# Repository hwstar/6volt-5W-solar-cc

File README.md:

***6volt-5W-solar-cc***
=============

This is a solar charge controller for use with 5 watt 6 volt solar panels.

**Introduction**

The project use a custom printed circuit board for the charge controller
power management electronics, and requires an external Arduino pro mini
to run the control firmware.

Setup in the lab:

The power management board design has the following features:

* PV input transient and reverse polarity protection
* Sensing for PV input voltage, converter output current, load current,
and battery voltage.
* PV Back feed protection using a dedicated MOSFET.
* PTC and reverse polarity protection on the battery connector.
* 3 sets of 3 pin connectors for loads. 
* 4 pin sense connector for current and voltage sensing to the Arduino
* 6 pin control connector for control signals from the Arduino
* Dedicated MOSFET for load switching.
* Switched and unswitched load configuration using solder jumpers.
* Double sided circuit board 5cm X 5cm

Front view of board:

Rear view of board:

**Board Blanks**

Board blanks are available on Tindie:

https://www.tindie.com/products/hwstarsr/6-volt-5-watt-solar-charge-controller

**Firmware**

The firmware is hosted as a separate project on my github pages.
See [fw-6volt-5W-solar-cc](https://github.com/hwstar/fw-6volt-5W-solar-cc). For more details on
the firmware features, please visit the firmware page.

**Python/tkinter utility**

A Python/tkinter utility is available to download variables from the
charge controller in real time using a Bus Pirate and an I2C interface.
This is also hosted on my github pages under 
[chargectrlr-python-buspirate](https://github.com/hwstar/chargectrlr-python-buspirate).

**License**

CC-BY-SA

**Disclaimer**

This project uses a lead acid battery. Please observe all safety 
precautions listed on the battery. Enclose this project in a metallic
fireproof enclosure. Keep internal temperatures within the operating
limits of the battery. Not responsible for life, or loss of property
under any circumstance!

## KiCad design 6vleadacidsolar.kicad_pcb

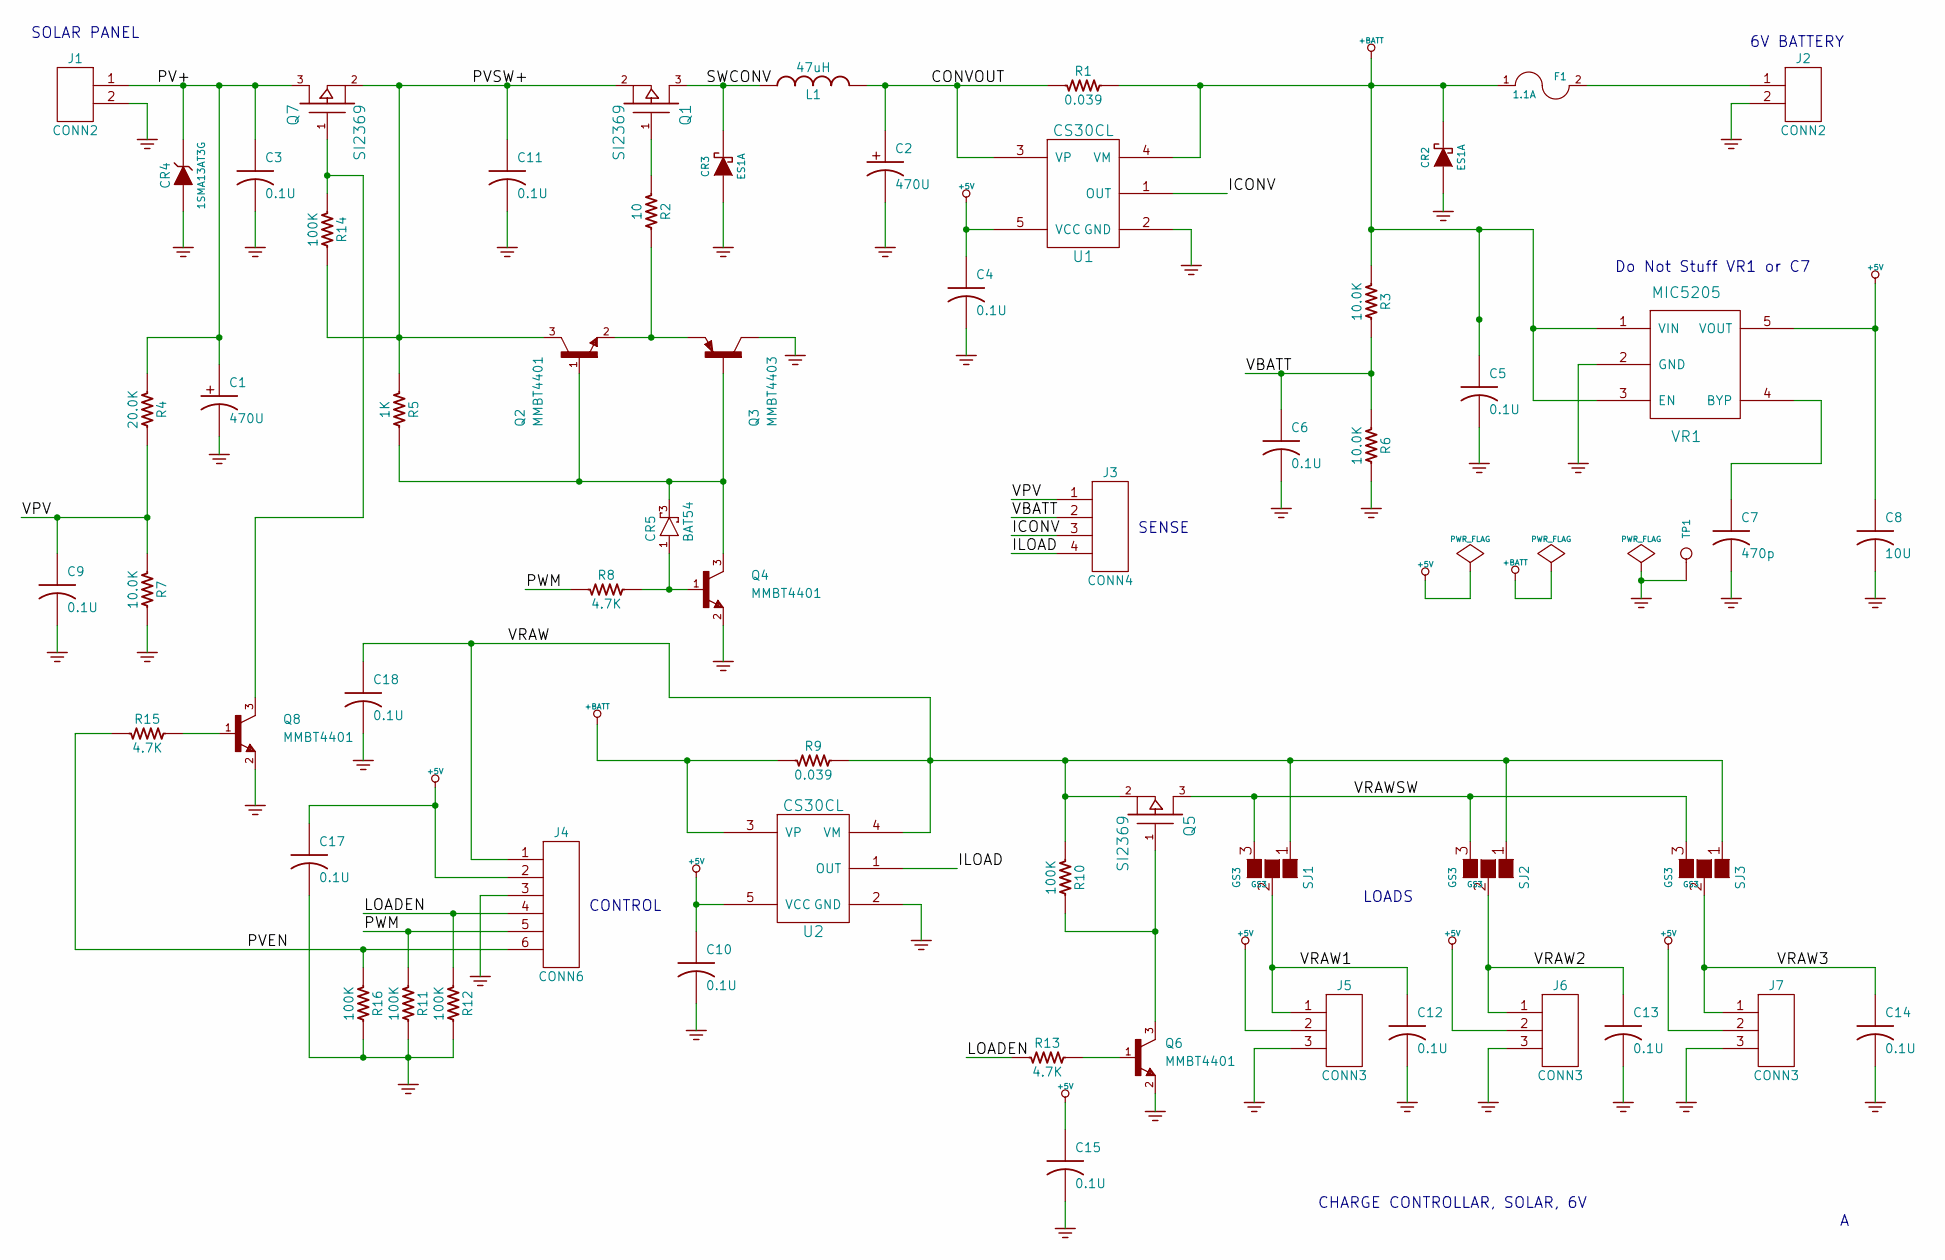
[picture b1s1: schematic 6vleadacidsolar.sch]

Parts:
C1, C2: 470U; MPN EMZJ160ADR471MHA0G
C3, C4, C5, C6, C9, C10, C11, C12, C13, C14, C15, C17, C18: 0.1U
C7: 470p
C8: 10U
CR2, CR3: ES1A; MPN ES1A-E3/61T
CR4: 1SMA13AT3G; MPN 1SMA13AT3G
CR5: BAT54; SOT23
F1: 1.1A; MPN MINISMD160F
J1, J2: CONN2
J3: CONN4
J4: CONN6
J5, J6, J7: CONN3
L1: 47uH; MPN SDE0805A-470K
Q1, Q5, Q7: SI2369; MPN SI2369DS-T1-E3
Q2, Q4, Q6, Q8: MMBT4401; SOT23
Q3: MMBT4403; custom-SOT23
R1, R9: 0.039; MPN KRL1220E-M-R039-F-T5
R2: 10
R3, R6, R7: 10.0K
R4: 20.0K
R5: 1K
R8, R13, R15: 4.7K
R10, R11, R12, R14, R16: 100K
SJ1, SJ2, SJ3: GS3
TP1: CONN_1
U1, U2: CS30CL; MPN CS30CL
VR1: MIC5205; SOT23-5

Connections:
+5V: C4.1, C8.1, C10.1, C15.1, C17.1, J4.2, J5.2, J6.2, J7.2, U1.5 (VCC), U2.5 (VCC), VR1.5 (VOUT)
+BATT: C5.1, CR2.2 (K), F1.1, R1.2, R3.1, R9.1, U1.4 (VM), U2.3 (VP), VR1.1 (VIN), VR1.3 (EN)
/CONVOUT: C2.1, L1.2, R1.1, U1.3 (VP)
/ICONV: J3.3, U1.1 (OUT)
/ILOAD: J3.4, U2.1 (OUT)
/LOADEN: J4.4, R12.1, R13.1
/PV+: C1.1, C3.1, CR4.2 (K), J1.1, Q7.3 (D), R4.1
/PVEN: J4.6, R15.1, R16.1
/PVSW+: C11.1, Q1.2 (S), Q2.3 (C), Q7.2 (S), R5.1, R14.2
/PWM: J4.5, R8.1, R11.1
/SWCONV: CR3.2 (K), L1.1, Q1.3 (D)
/VBATT: C6.1, J3.2, R3.2, R6.1
/VPV: C9.1, J3.1, R4.2, R7.1
/VRAW: C18.1, J4.1, Q5.2 (S), R9.2, R10.1, SJ1.1 (G1), SJ2.1 (G1), SJ3.1 (G1), U2.4 (VM)
/VRAW1: C12.1, J5.1, SJ1.2 (G2)
/VRAW2: C13.1, J6.1, SJ2.2 (G2)
/VRAW3: C14.1, J7.1, SJ3.2 (G2)
/VRAWSW: Q5.3 (D), SJ1.3 (G3), SJ2.3 (G3), SJ3.3 (G3)
GND: C1.2, C2.2, C3.2, C4.2, C5.2, C6.2, C7.2, C8.2, C9.2, C10.2, C11.2, C12.2, C13.2, C14.2, C15.2, C17.2, C18.2, CR2.1 (A), CR3.1 (A), CR4.1 (A), J1.2, J2.2, J4.3, J5.3, J6.3, J7.3, Q3.3 (C), Q4.2 (E), Q6.2 (E), Q8.2 (E), R6.2, R7.2, R11.2, R12.2, R16.2, TP1.1, U1.2 (GND), U2.2 (GND), VR1.2 (GND)
unnamed: C7.1, VR1.4 (BYP)
unnamed: Q6.1 (B), R13.2
unnamed: Q5.1 (G), Q6.3 (C), R10.2
unnamed: Q2.2 (E), Q3.2 (E), R2.2
unnamed: Q1.1 (G), R2.1
unnamed: F1.2, J2.1
unnamed: CR5.1 (A), Q4.1 (B), R8.2
unnamed: CR5.3 (C), Q2.1 (B), Q3.1 (B), Q4.3 (C), R5.2
unnamed: Q8.1 (B), R15.2
unnamed: Q7.1 (G), Q8.3 (C), R14.1

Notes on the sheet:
6V BATTERY
SOLAR PANEL
CONTROL
SENSE
LOADS
CHARGE CONTROLLAR, SOLAR, 6V
Do Not Stuff VR1 or C7

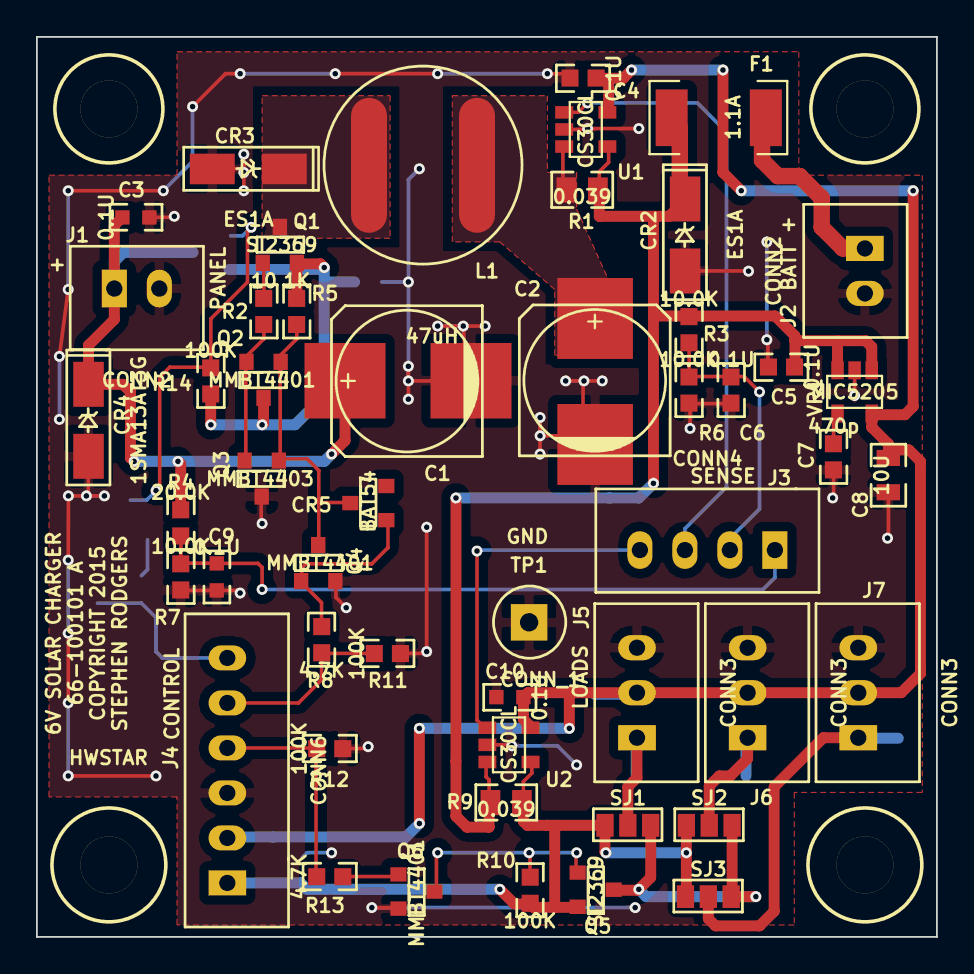
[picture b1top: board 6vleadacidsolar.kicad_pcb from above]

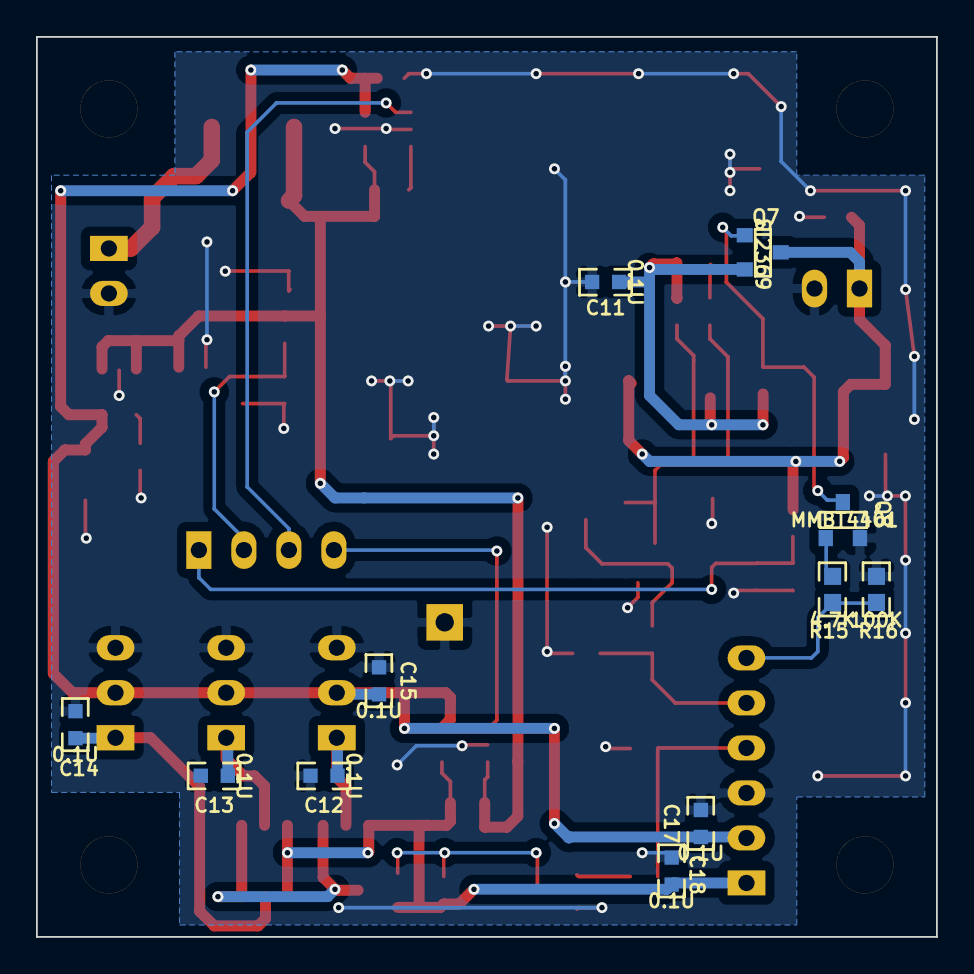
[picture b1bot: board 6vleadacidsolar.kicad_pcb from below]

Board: 2 copper layers, 50.0 x 50.0 mm, 65 parts (11 on the bottom side), 29 nets.

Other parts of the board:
MTGHOLE125, MTGHOLE125#2, MTGHOLE125#3, MTGHOLE125#4: VAL**; MTGHOLE125

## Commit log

2015-05-29 Initial Checkin
2015-05-29 Fix grammatical error
2015-05-29 Fix typos
2015-06-22 Fix typo in BOM, update project file
2015-06-23 Schematic cleanup, add part numbers to parts in schematic
2015-06-23 add rescue lib
2015-06-27 Add missing letter to F1 MPN
2015-06-27 Correct solder jumper item

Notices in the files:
6vleadacidsolar.kicad_pcb:
COPYRIGHT 2015
